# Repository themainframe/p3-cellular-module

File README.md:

# GPD Pocket 3 Cellular Module

This is a plug-in cellular module for the [GPD Pocket 3](https://gpd.hk/gpdpocket3). It provides LTE Cat. 4 cellular connectivity using a Quectel EC25 (or compatible) module.

It's still a little bit of a prototype at this stage, but initial results are promising!

You can read more about it [on my blog](https://damow.net/gpd-pocket-3-cellular-module).

## Stackup & BOM

4 layers. JLC JLC04101H-7628 Impedance Controlled FR4.

HTML BOMs can be found in the `bom/` directory.

## Questions?

Open an issue or drop me an email - `me@` my blog domain.

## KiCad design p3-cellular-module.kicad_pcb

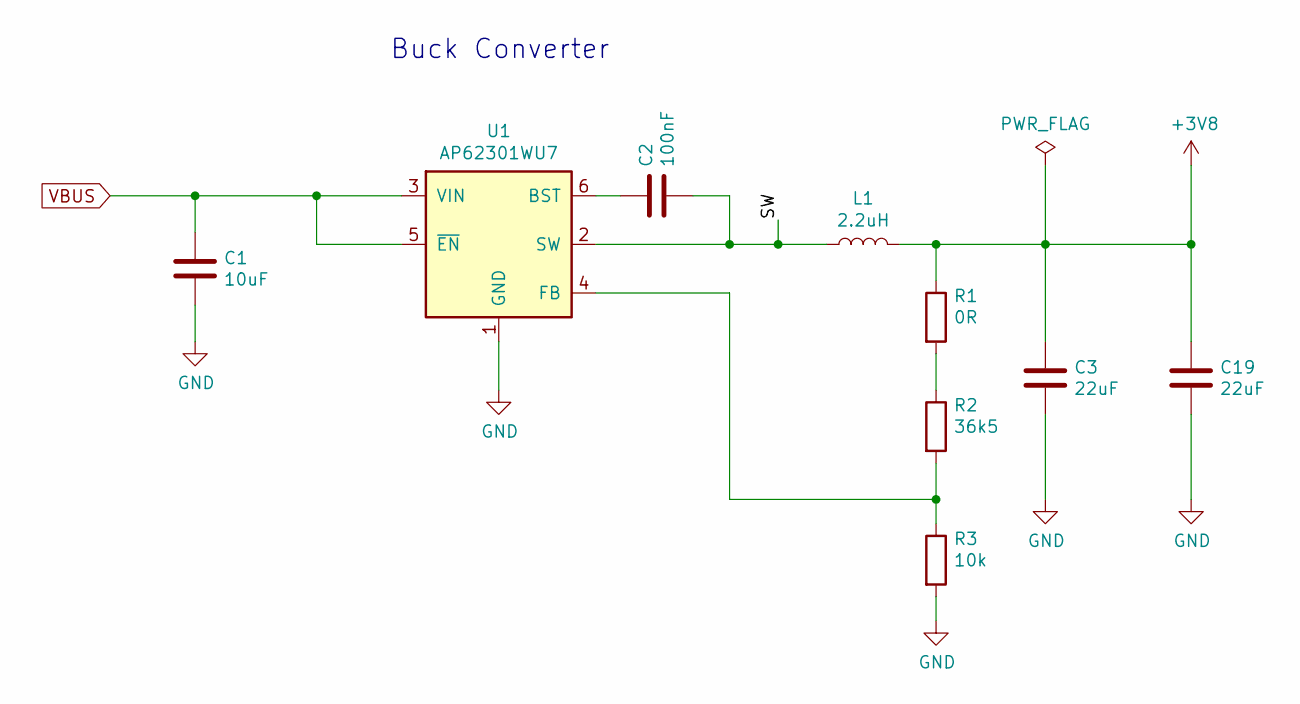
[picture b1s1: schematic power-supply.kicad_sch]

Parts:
C1: 10uF; C_0805_2012Metric; MPN GRM21BR71A106KA73K
C2: 100nF; C_0603_1608Metric; MPN C0603C104K3RAC
C3, C19: 22uF; C_1210_3225Metric; MPN CL32B226MOJNNNE
L1: 2.2uH; L_Coilcraft_XAL5030; MPN XAL5030-222MEC
R1: 0R; R_0603_1608Metric
R2: 36k5; R_0603_1608Metric; MPN CRCW060336K5FKEA
R3: 10k; R_0603_1608Metric
U1: AP62301WU7; TSOT-23-6; MPN AP62301WU-7

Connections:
+3V8: C3.1, C19.1, L1.2, R1.1; also elsewhere on the board
/Power Supply/SW: C2.2, L1.1, U1.2 (SW)
GND: C1.2, C3.2, C19.2, R3.2, U1.1 (GND); also elsewhere on the board
unnamed: C2.1, U1.6 (BST)
unnamed: R1.2, R2.1
unnamed: R2.2, R3.1, U1.4 (FB)
VBUS: C1.1, U1.3 (VIN), U1.5 (~EN); also elsewhere on the board

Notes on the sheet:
Buck Converter

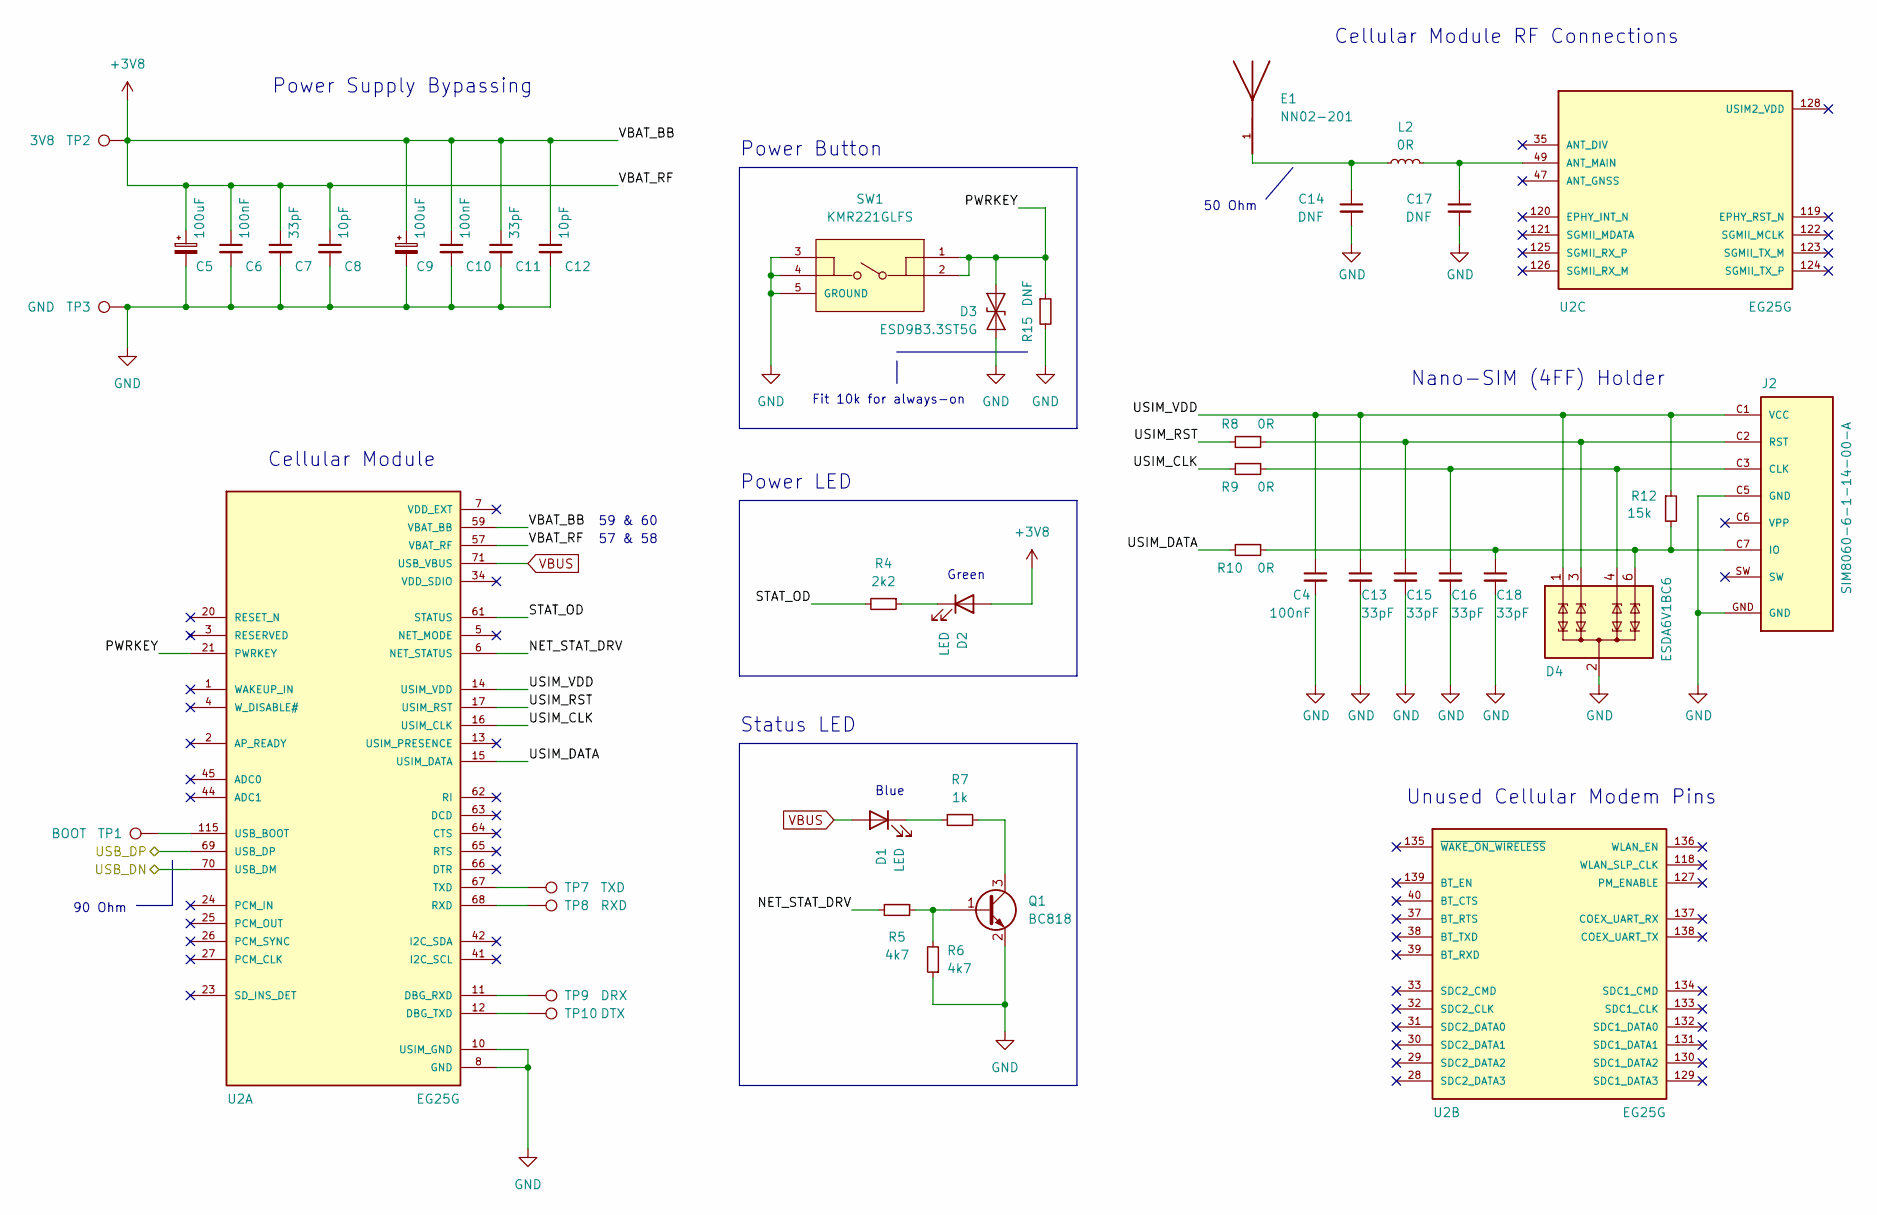
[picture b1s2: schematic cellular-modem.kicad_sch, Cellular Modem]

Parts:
C4, C6, C10: 100nF; C_0603_1608Metric; MPN C0603C104K3RAC
C5, C9: 100uF; CP_EIA-3528-21_Kemet-B; MPN TCJB107M006R0040
C7, C11, C13, C15, C16, C18: 33pF; C_0603_1608Metric; MPN 06035A330KAT2A
C8, C12: 10pF; C_0603_1608Metric
C14, C17: DNF; C_0603_1608Metric
D1, D2: LED; LED_0603_1608Metric
D3: ESD9B3.3ST5G; D_0603_1608Metric; MPN ESD9B3.3ST5G
D4: ESDA6V1BC6; SOT-23-6; MPN ESDA6V1BC6
E1: NN02-201; XCVR_NN02-201; MPN NN02-201
J2: SIM8060-6-1-14-00-A; GCT_SIM8060-6-1-14-00-A; MPN SIM8060-6-1-14-00-A
L2: 0R; L_0603_1608Metric
Q1: BC818; SOT-23; MPN BC818-40
R4: 2k2; R_0603_1608Metric
R5, R6: 4k7; R_0603_1608Metric
R7: 1k; R_0603_1608Metric
R8, R9, R10: 0R; R_0603_1608Metric
R12: 15k; R_0603_1608Metric
R15: DNF; R_0603_1608Metric
SW1: KMR221GLFS; CK-KMR221GLFS-MFG; MPN KMR221GLFS
TP1: BOOT; TestPoint_Pad_1.0x1.0mm
TP2: 3V8; TestPoint_Pad_1.0x1.0mm
TP3: GND; TestPoint_Pad_1.0x1.0mm
TP7: TXD; TestPoint_Pad_1.0x1.0mm
TP8: RXD; TestPoint_Pad_1.0x1.0mm
TP9: DRX; TestPoint_Pad_1.0x1.0mm
TP10: DTX; TestPoint_Pad_1.0x1.0mm
U2: EG25G; XCVR_EG25G; MPN EG25G

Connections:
+3V8: C5.1, C6.1, C7.1, C8.1, C9.1, C10.1, C11.1, C12.1, D2.2 (A), TP2.1, U2.57 (VBAT_RF), U2.58 (VBAT_RF), U2.59 (VBAT_BB), U2.60 (VBAT_BB); also elsewhere on the board
/Cellular Modem/NET_STAT_DRV: R5.2, U2.6 (NET_STATUS)
/Cellular Modem/PWRKEY: D3.2 (A2), R15.1, SW1.1, SW1.2, U2.21 (PWRKEY)
/Cellular Modem/STAT_OD: R4.2, U2.61 (STATUS)
/Cellular Modem/USB_DN: U2.70 (USB_DM); also elsewhere on the board
/Cellular Modem/USB_DP: U2.69 (USB_DP); also elsewhere on the board
/Cellular Modem/USIM_CLK: R9.2, U2.16 (USIM_CLK)
/Cellular Modem/USIM_DATA: R10.2, U2.15 (USIM_DATA)
/Cellular Modem/USIM_RST: R8.2, U2.17 (USIM_RST)
/Cellular Modem/USIM_VDD: C4.1, C13.1, D4.1 (TVS1), J2.C1 (VCC), R12.1, U2.14 (USIM_VDD)
GND: C4.2, C5.2, C6.2, C7.2, C8.2, C9.2, C10.2, C11.2, C12.2, C13.2, C14.2, C15.2, C16.2, C17.2, C18.2, D3.1 (A1), D4.2 (COM), D4.5 (COM), J2.C5 (GND), J2.GND, Q1.2 (E), R6.1, R15.2, SW1.3, SW1.4, SW1.5 (GROUND), TP3.1, U2.8 (GND), U2.9 (GND), U2.10 (USIM_GND), U2.19 (GND), U2.22 (GND), U2.36 (GND), U2.46 (GND), U2.48 (GND), U2.50 (GND), U2.51 (GND), U2.52 (GND), U2.53 (GND), U2.54 (GND), U2.56 (GND), U2.72 (GND), U2.85 (GND), U2.86 (GND), U2.87 (GND), U2.88 (GND), U2.89 (GND), U2.90 (GND), U2.91 (GND), U2.92 (GND), U2.93 (GND), U2.94 (GND), U2.95 (GND), U2.96 (GND), U2.97 (GND), U2.98 (GND), U2.99 (GND), U2.100 (GND), U2.101 (GND), U2.102 (GND), U2.103 (GND), U2.104 (GND), U2.105 (GND), U2.106 (GND), U2.107 (GND), U2.108 (GND), U2.109 (GND), U2.110 (GND), U2.111 (GND), U2.112 (GND); also elsewhere on the board
unnamed: C14.1, E1.1, L2.1
unnamed: C15.1, D4.3 (TVS2), J2.C2 (RST), R8.1
unnamed: C16.1, D4.4 (TVS3), J2.C3 (CLK), R9.1
unnamed: C17.1, L2.2, U2.49 (ANT_MAIN)
unnamed: C18.1, D4.6 (TVS4), J2.C7 (IO), R10.1, R12.2
unnamed: D1.1 (K), R7.1
unnamed: D2.1 (K), R4.1
unnamed: Q1.1 (B), R5.1, R6.2
unnamed: Q1.3 (C), R7.2
unnamed: TP1.1, U2.115 (USB_BOOT)
unnamed: TP7.1, U2.67 (TXD)
unnamed: TP8.1, U2.68 (RXD)
unnamed: TP9.1, U2.11 (DBG_RXD)
unnamed: TP10.1, U2.12 (DBG_TXD)
VBUS: D1.2 (A), U2.71 (USB_VBUS); also elsewhere on the board

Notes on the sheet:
Status LED
57 & 58
59 & 60
Green
Unused Cellular Modem Pins
Blue
90 Ohm
50 Ohm
Power LED
Power Supply Bypassing
Nano-SIM (4FF) Holder
Power Button
Cellular Module
Cellular Module RF Connections
Fit 10k for always-on

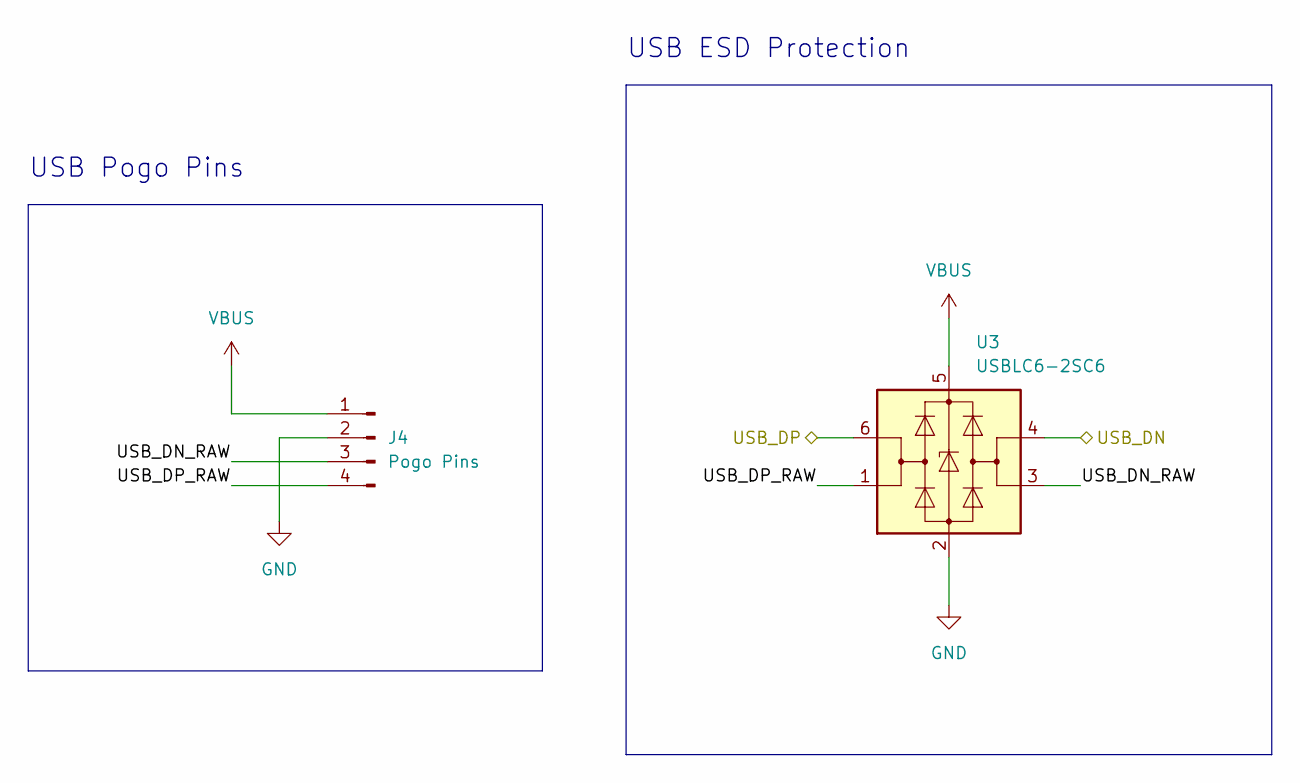
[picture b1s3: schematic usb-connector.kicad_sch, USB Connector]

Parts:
J4: Pogo Pins; PogoPins; MPN 836-22-004-10-001101
U3: USBLC6-2SC6; SOT-23-6; MPN USBLC6-2SC6

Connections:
/Cellular Modem/USB_DN: U3.4 (I/O2); also elsewhere on the board
/Cellular Modem/USB_DP: U3.6 (I/O1); also elsewhere on the board
/USB Connector/USB_DN_RAW: J4.3, U3.3 (I/O2)
/USB Connector/USB_DP_RAW: J4.4, U3.1 (I/O1)
GND: J4.2, U3.2 (GND); also elsewhere on the board
VBUS: J4.1, U3.5 (VBUS); also elsewhere on the board

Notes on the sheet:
USB ESD Protection
USB Pogo Pins

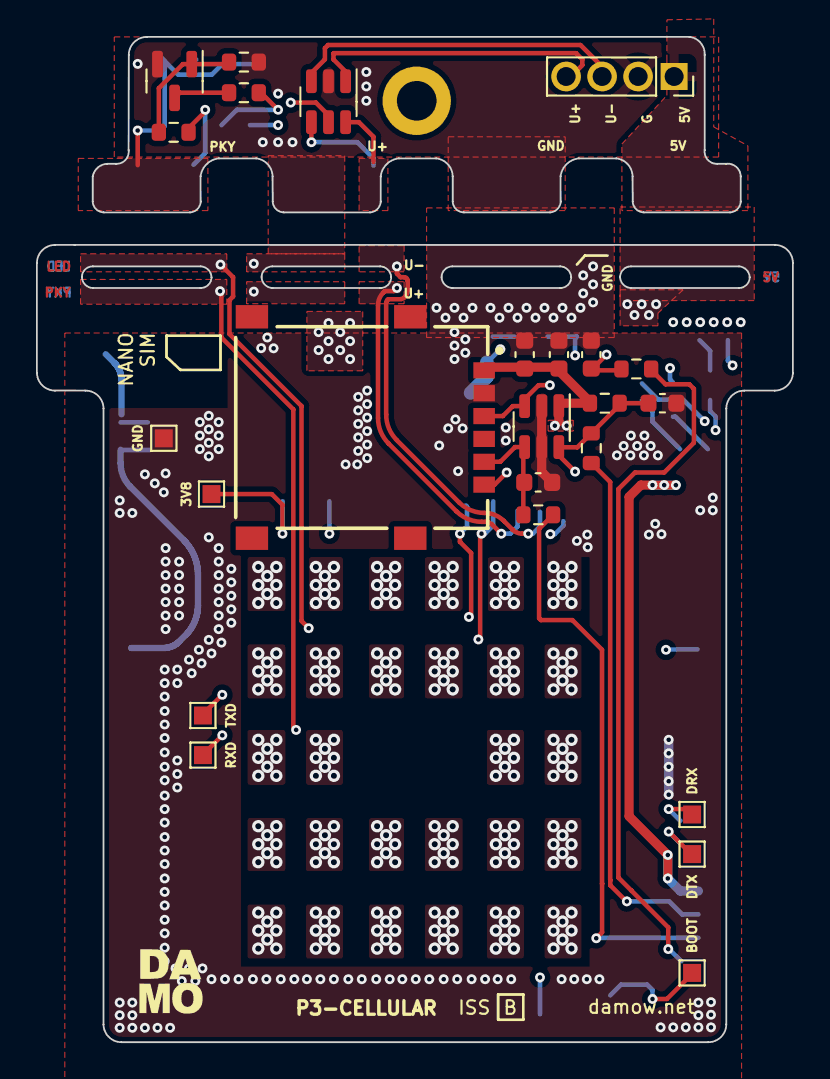
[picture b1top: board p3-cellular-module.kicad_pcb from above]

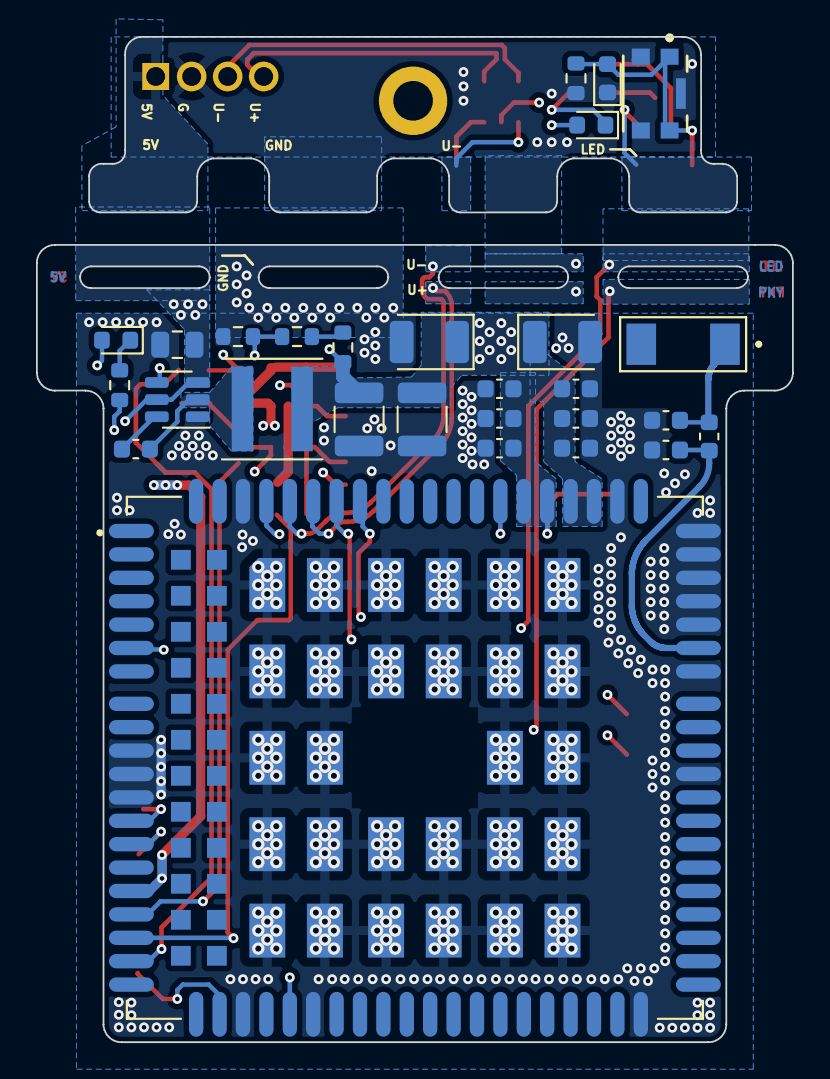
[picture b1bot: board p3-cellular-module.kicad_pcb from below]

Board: 4 copper layers, 42.0 x 55.8 mm, 52 parts (28 on the bottom side), 32 nets.

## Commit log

2022-06-17 Add: Improved layout
2022-06-19 Update: Ground plane setup
2022-10-29 Add: Board size changes
2022-10-30 Add: Mechanical changes pre-rev1 production run
2022-11-25 Change: Separate boards rather than using mousebites
2023-06-10 Add: Gerbers for Rev2
2023-06-10 Add: README and Prototype Image
